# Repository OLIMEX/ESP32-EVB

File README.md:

# ESP32-EVB

ESP32 wifi / BLE development board with Ethernet, relays, microSD card, CAN, infrared, Li-Po charger, GPIOs.

Product page: https://www.olimex.com/Products/IoT/ESP32/ESP32-EVB/open-source-hardware

Open-source hardware board made with open-source CAD software. Comes with either ESP32-WROOM-32E or ESP32-WROOM-32UE module, depending on variant. Board vairants are:

| Board variant | ESP32 module  | External antenna  | Temperature range |
| ------------- | ------------- | -------------  | ------------- |
| ESP32-EVB     | ESP32-WROOM-32E  | No  | 0-70°C  |
| ESP32-EVB-EA  | ESP32-WROOM-32UE  | Yes  | 0-70°C  |
| ESP32-EVB-EA-IND  | ESP32-WROOM-32UE  | Yes  | -40+85°C |
| ESP32-EVB-IND  | ESP32-WROOM-32E  | No  | -40+85°C |

ESP32-EVB - ESP32-WROOM-32E module, no external antenna, commercial temeprature range 0-70°C

ESP32-EVB-EA - ESP32-WROOM-32UE module, fitting external antenna, commercial temeprature range 0-70°C

ESP32-EVB-EA-IND - ESP32-WROOM-32UE module, fitting external antenna, industrial temeprature range -40+85°C

ESP32-EVB-IND - ESP32-WROOM-32E module, no external antenna, industrial temeprature range -40+85°C

You can find design hardware sources, schematic exports, BOMs, and more, in the "HARDWARE" folder.

You can find ESP-IDF and Arduino IDE examples, in the "SOFTWARE" folder.

# FAQ

---

**Q:** I have some trouble downloading my code to ESP32-EVB. Is there a way to force boot mode?

**A:** By default the board comes without BOOT button functioanlity. However, we have providedan option to can convert user BUT1 into BOOT button to force button but this requires hardware change and soldering. Soldering experience is required since it is a tight spot. You need to perform two changes:

- Solder the pads of R46 together (or solder 0R resistor in 0603 size in the R46 position there);
- Unsolder R14 and solder its pads together (or again solder 0R resistor in 0603 size in the R14 position).

After the two changes, to manually force boot mode, hold button BUT1 then reset the board with RST1. Both R46 and R14 are near the button BUT1. Notice that the button will still act as user button after the initial boot sequence. You can find more about what changing these resistors does if you inspect the schematic.

---

**Q:** The Ethernet doesn't start after a restart, it throws "init phy failed" error. What should I do?

**A:** Ethernet might hang of initialized too quickly after a reset. Add some delay at the start of the code before the Ethernet initialization. For example, if you are using the default Arduino IDE demo for LAN8720 try adding delay () after Serial.begin(), as shown below:
```
void setup()
{
Serial.begin(115200);
delay (2000);
WiFi.onEvent(WiFiEvent);
ETH.begin();
}
```

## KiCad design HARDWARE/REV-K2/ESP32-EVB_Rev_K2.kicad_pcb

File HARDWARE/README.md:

# ESP32-EVB

Hardware revisions changes:

- revision A - internal, not released
- revision B - initial public release
- revision C - changes:

1. MicroUSB connector moved back, 40 mils to the middle of the board.
2. All mounting holes are now connected to GND.
3. Improved the ground layer around the infra red's pads and wires.

- revision C1 - changes:

1. Changed R38 from 10k/0603 to 100k/0603 to lower the time without clock
2. Changed C28 from 100n/0603 to 10n/0603 to increase the time in reset

- revision D - changes:

1. Added a resistor (1k) between OSC_DIS and reset of the PHY.
2. Added option to use MCP2562-E/SN and SN65HVD230D upotreba -> R58(NA/R0603)!
4. U2 be promeneno ot SY8009AAAC(SOT23-5) na SY8089AAAC(SOT23-5).
5. FET1 and FET2 were changed from IRLML6402 to WPM2015-3/TR.

- revision D1 - changes:

1. Removed C18(10uF)
2. U8 changed from BD5230G-TR(SSOP5/SOT-23-5) to NCP303LSN27T1G(SOT-23-5), due to unavailability;
3. C28 changed from 100nF/50V/20%/Y5V/C0603 to 470nF/16V/10%/X7R/C0603, because of the U8 change;

- revision D2 - changes:

1. U6 changed from MCP2551-I/SN(SOIC-8_150mil) to MCP2562-E/SN(SOIC-8_150mil)
2. R58 changed from NA/R0603 to 0R/R0603.

- revision E - changes:

MCP2551 got "Not recommended for new designs" status so it is replaced with MCP2562 and this lead to:

1. R58(0R/R0603) was deleted and U6's pin<5> was connected to +3.3V.
2. R52(680R/R0603) was deleted.
3. R50(330R/R0603) and R51(330R/R0603) were deleted.
4. The MCP2562-E_SN(SOIC-8_150mil)'s symbol was updated, i,.e. U6's component was exchanged with 2562!

Changes related to the problems with ethernet PHY:

5. The following components were added to enable powering on the PHY after the 50MHz oscillator has been started: L5(NA(FB0805/600R/2A)), FET3(WPM2015-3/TR), FET4(BSS138), C29(22uF/6.3V/20%/X5R/C0603), R50(1k/R0603) and R51(10k/R0603).

Changes related to optimizations:

6. R26(330R/R0603) and R27(330R/R0603) were changed to 220R/R0603 to reserve a feeder.
7. C1 was changed from 47uF/6.3V/20%/X5R/C0805 to NA(47uF/6.3V/20%/X5R/C0805).	
8. C3 was changed from 47uF/6.3V/20%/X5R/C0805 to NA(47uF/6.3V/20%/X5R/C0805).

- revision F - changes:

1. BUT1 and RST1 new packages.
2. Minor PCB routing optimizations.
3. All footprints were updated.

- revision G - internal, not released

1. Changed the Li-Po charger to BL4054B (was MCP73833 previously).

- revision H - limited release, changes:

1. CH340 now powered only from USB (not from battery). Added D7 and D8 on TX/RX, levels are adjusted via R35 and R40. Pin #20 now disconnected. SY8089AAAC(SOT23-5) devider now R20 49.9k and R19 220k. R24 now 470ê.
2. Added battery voltage sense option. This is controlled with jumper BAT/BUT1, C30, R9, and R10. It is not enabled by default to maintain compatiblity with previous revisions.
3. Added 3D models of the components.
4. L2 now 2.2uH/1.5A/DCR=72mR/20%/3.00x3.00x1.50mm/CD32(NR3015T2R2M). Some improvements on ESP-WROOM-32_MODULE package.

- revision H1 - released, changes:

Improved start up for certain hardware setups. Revision H1 has same PCB as revision H (and the PCB of revision H1 says "H") but couple of component changes:

1. Changed R24 from 470k/0603 to 1k/0603, the 1k resistor is soldered over the 470k one to reduce chances of damage.

- revsion I - released, changes:

Applied the changes from revision H1 to the PCB and the design, and further improved start-up reliability by adding a capacitor:

1. Added C31(1uF/10V/10%/X5R/C0603) on the ESP_EN signal and R24's value changed from 1k/0603 to 10k/0603;
2. Added several text lables at the botttom of the board about CAN's connector signals and the battery polarity.

- revision I1 - released, changes:

1. Changed C18 from NA(10uF/6.3V/20%/X5R/C0603) to 1nF/50V/5%/NPO(COG)/C0603 - this improves Ethernet reliability during relay switcing;

- revision I2 - released, changes:

1. Changed U8, from NCP303LSN27T1G(SOT-23-5) to NCP303LSN18T1G(SOT-23-5).

- revision I3 - released, changes:

1. Changed U6 from MCP2562-E/SN(SOIC-8_150mil) to SIT1042T/3(SOIC-8_150mil).

- revision I4 - released

1. Changed U2 value to NCV303LSN23T1G.

- revision J - not released

1. Due to global unavailability of MCP2562-E/SN chips, it was necessary to adjust the CAN schematic for compatiblity with MCP2551/SIT1050 too. Following changes were required:
- U6 changed from MCP2562-E/SN(SOIC-8_150mil) to SIT1050T(SOIC-8_150mil);
- Added R12, NA/R0603;
- Added R13, 330R/R0603;
- Added R15, 680R/R0603;
2. CE sign added in the PCB;
3. Changed C18 from NA(10uF/6.3V/20%/X5R/C0603) to 1nF/50V/5%/NPO(COG)/C0603 - this improves Ethernet behavior during relay switching;
4. Added U11(VDA2710NTA(SOT-23)), D10(BAT54A(SOT23-3)), R58(49.9R/1%/R0402), R52(220k/R0603) and C32(1uF/10V/10%/X5R/C0603), so that we can have option to replace the reset chip NCP303LSN27T1G(SOT-23-5). Changed U8 to (NA(NCP303LSN27T1G(SOT-23-5))) and C28 to NA(470nF/16V/10%/X7R/C0603);
5. Added D9(1N5819S4(SOD-123)), to rptoect ESP_EN from 4.2V surge during programming; also to protect C32 gettomg cjarged from DTR output of CH340, else new reset schematic (VDA2710NTA) has random timing after pressing reset button;
6. Added ESD protection on the Ethernet, TVS1(ESDS314DBVR(SOT-23-5));
7. R28, R31, R32, and R33 changed from 49.9R/1%/R0603 to 49.9R/1%/R0402;
8. U7 changed from RPM7236-H8 to VS1838B.

- revision K - released

1. Labelling improvements;
2. Removed "GPIO4" from the "Internal Bootstrapping Resistors" table.

- revision K1 - released

1. Changed reset IC from VDA2710NTA(SOT-23)to HX7027 (due to unavailability of VDA2710NTA).
2. HX7027 has slightly bigger consumption and when powered trought R52 the voltage might get too low; so also changed R52 from 220k to 100k.

- revision K2 - released
------
1. Changed battery chager to TP4054-42-SOT25-R;
2. Changed R8 from 2k to 10k to reduce battery charger current to 100mA.

- revision L - released
------

1. Migated the whole project to KiCad7;
2. R57 deleted to reduce possible environment noise picking in combination with relay switching;
3. Relays changed;
4. U2-SY8089 changed to TPS62A02ADRLR(SOT-563-6);
5. CH340 changed with smaller variant ch340X.

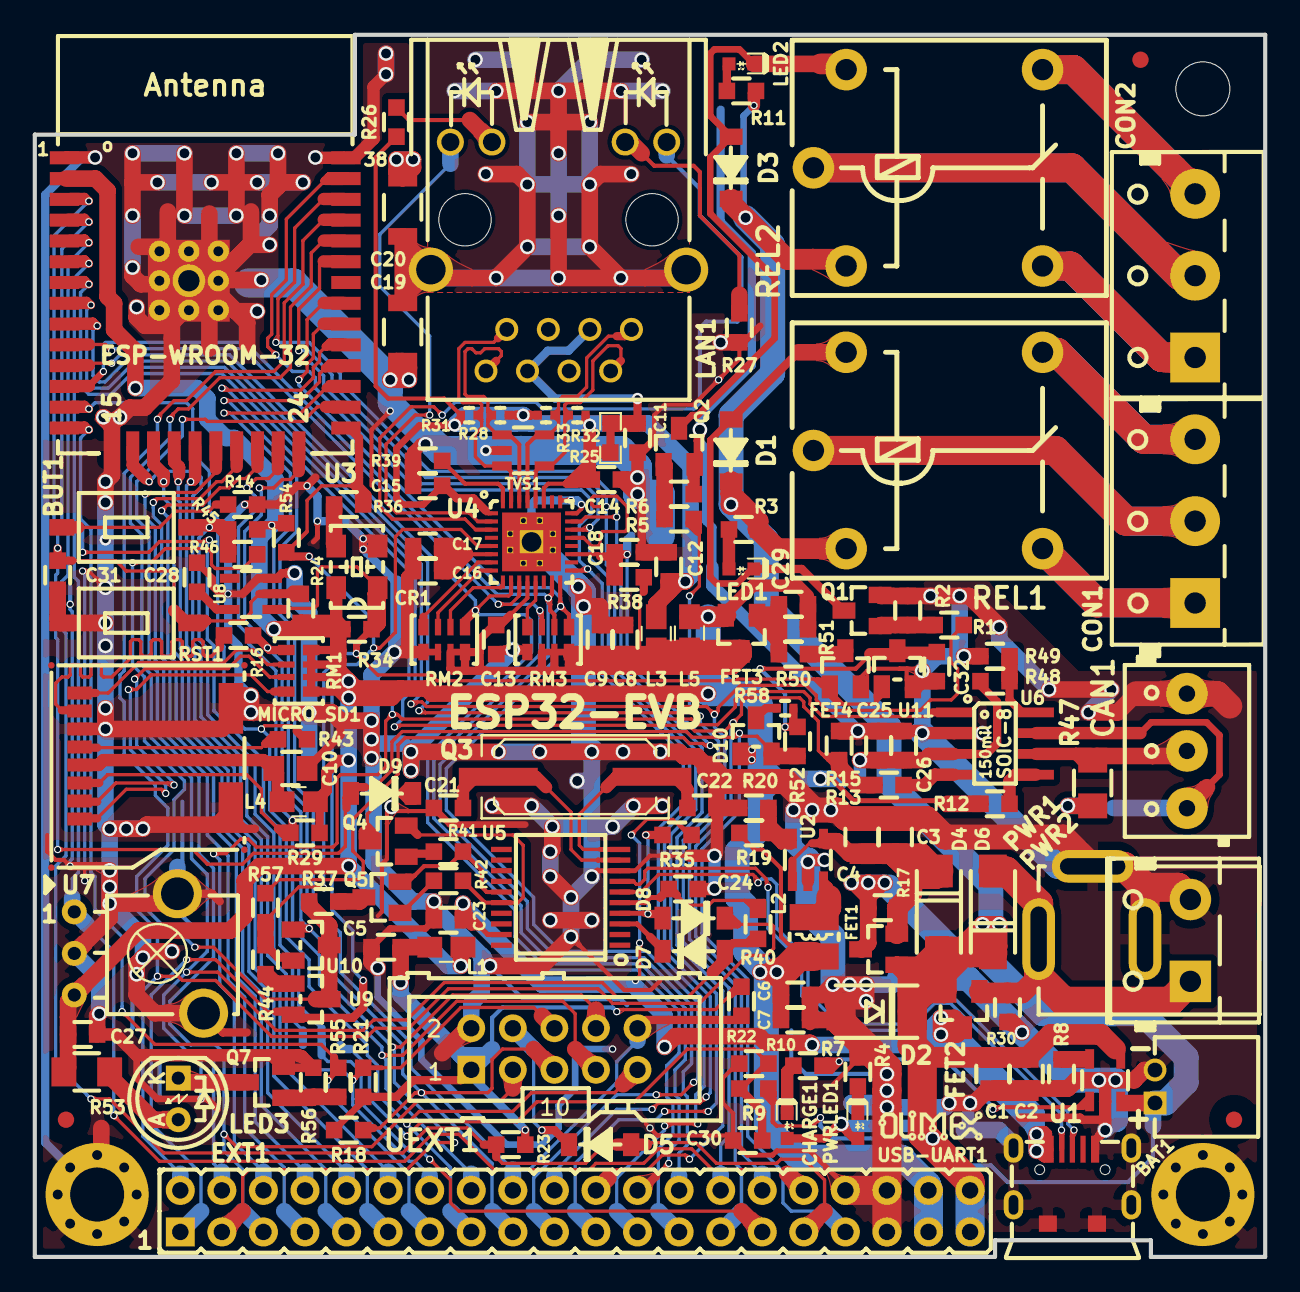
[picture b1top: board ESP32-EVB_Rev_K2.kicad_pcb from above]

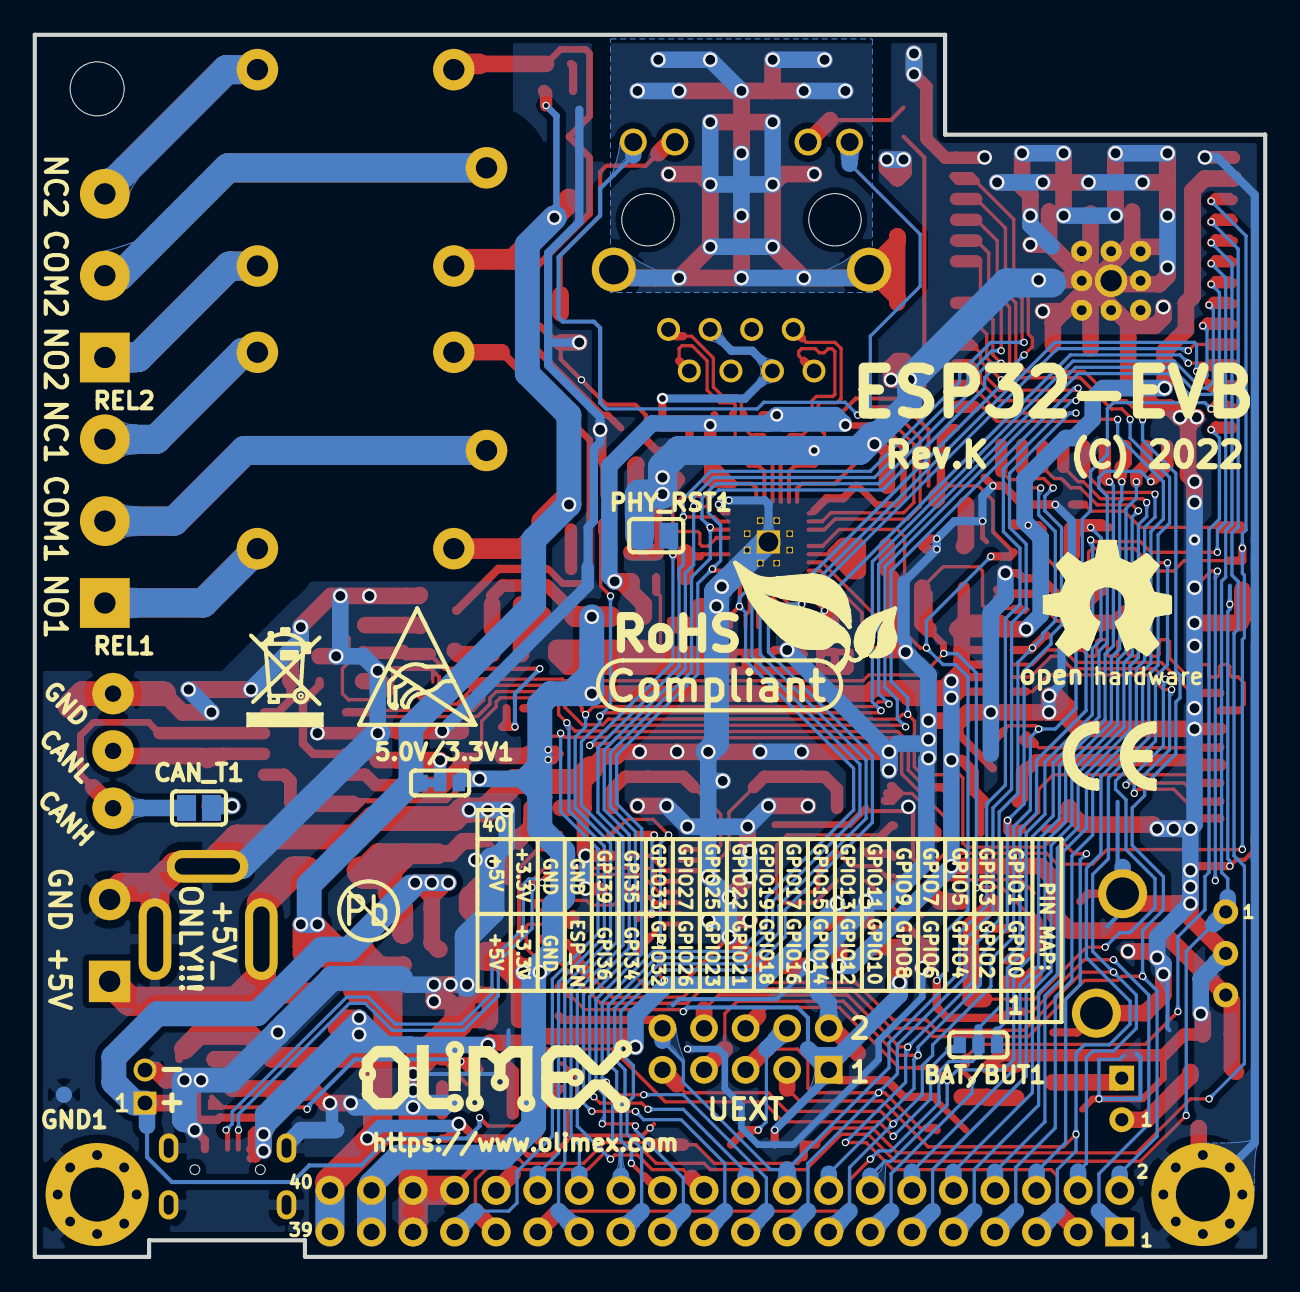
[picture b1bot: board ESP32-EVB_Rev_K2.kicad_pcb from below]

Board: 2 copper layers, 75.2 x 74.7 mm, 170 parts (12 on the bottom side), 120 nets.

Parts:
5.0V/3.3V1: Closed(1-2)/Opened(2-3); SJ_2_SMALL_12_TIED
BAT1: DW02R; LIPO_BAT-CON2DW02R
BAT/BUT1: Opened(2-3)/Soldered(1-2); SJ_2_SMALL
BUT1: T1107A(6x3,8x2,5MM)
C1, C3: NA(47uF/6.3V/20%/X5R/C0805); C_0805_5MIL_DWS
C2, C4, C10: 47uF/6.3V/20%/X5R/C0805; C_0805_5MIL_DWS
C5, C6, C7, C8, C9, C12, C23, C29: 22uF/6.3V/20%/X5R/C0603; C_0603_5MIL_DWS
C11, C13, C14, C15, C17, C24, C25, C27, C30: 100nF/50V/20%/Y5V/C0603; C_0603_5MIL_DWS
C16: 2.2uF/6.3V/10%/X5R/C0603; C_0603_5MIL_DWS
C18: 1nF/50V/5%/NPO(COG)/C0603; C_0603_5MIL_DWS
C19: 1nF/2000V/10%/X7R/C1206; C_1206_5MIL_DWS_ISO
C20: NA(1nF/2000V/10%/X7R/C1206); C_1206_5MIL_DWS_ISO
C21, C22: 27pF/50V/5%/C0G/C0603; C_0603_5MIL_DWS
C26: 10uF/6.3V/20%/X5R/C0603; C_0603_5MIL_DWS
C28: NA(470nF/16V/10%/X7R/C0603); C_0603_5MIL_DWS
C31, C32: 1uF/10V/10%/X5R/C0603; C_0603_5MIL_DWS
CAN1: TB3-3.5ММ(HD-351 3P); TB3-3.5mm
CAN_T1: Opened; SJ
CHARGE1: LED/Yellow/0603; LED_0603_KA
CON1, CON2: DG306-5.0-3P; TB3-DG306-5.0_3P
CR1: Q50MHz/25ppm/3V/4P/5x3.2mm; 5032-4P_HCX-3S
D1, D3, D5, D7, D8, D9: 1N5819S4(SOD-123); SOD-123_1C-2A_KA
D2: SMBJ6.0A(DO-214AA); DO214AA_1(K)-2(A)
D4, D6: 1N5822/SS34/SMA; SMA-KA
D10: BAT54A(SOT23-3); SOT23-3
EXT1: NA(HN2x20); HN2x20
FET1, FET2, FET3: WPM2015-3/TR; SOT23
FET4: BSS138; SOT23
Fid1, Fid2, Fid3: Fiducial1x3
GND1: TESTPAD; TESTPAD_40-ROUND
L1, L3, L4: 600R/2A/UPZ2012E-601-2R0TF; L_0805_5MIL_DWS
L2: 2.2uH/NRS3015T2R2MNGH; CD32
L5: NA(FB0805/600R/2A); L_0805_5MIL_DWS
LAN1: RJLBC-060TC1(LPJ4013EDNL); RJLBC-060TC1
LED1, LED2: LED/GREEN/0603; LED_0603_KA
LED3: LED/IR333-A/5mm; LED-5mm-PTH-AK
Logo-OSHW: LOGO_OPENHARDWARE_8x8
Logo-Olimex-Big: OLIMEX_LOGO_TB
Logo-Olimex_Small: LOGO_OLIMEX_80
MH1: Mounting_hole_Shield_3.3mm; Mounting_hole_3.3mm
MH2, MH3: Mounting_hole_Shield_3.3mm
MICRO_SD1: TFC-WXCP11-08-LF
PHY_RST1: Opened; SJ
PWR1: PWRJ-2mm(YDJ-1134); PWRJ-2mm(YDJ-1136)
PWR2: NA(TB2 DG306-5.0-2P); TB2-DG306-5.0_2P
PWRLED1: LED/RED/0603; LED_0603_KA
Q1, Q2, Q4, Q5, Q7: BC817-40(SOT23); SOT23
Q3: Q12MHz/2P/20ppm/20pF/HU49SM; Q_49U3HMS
R1, R5, R41, R42, R50, R55: 1k/R0603; R_0603_5MIL_DWS
R2, R6, R22, R23, R24, R29, R30, R34, R35, R38, R40, R45, R49, R51, R56: 10k/R0603; R_0603_5MIL_DWS
R3, R4, R7, R11, R18, R21: 2.2k/R0603; R_0603_5MIL_DWS
R8: 2k/1%/R0603; R_0603_5MIL_DWS
R9, R10: 470k/R0603; R_0603_5MIL_DWS
R12, R17, R44, R46, R48, R54: NA/R0603; R_0603_5MIL_DWS
R13: 330R/R0603; R_0603_5MIL_DWS
R14, R16, R26, R27, R37: 220R/R0603; R_0603_5MIL_DWS
R15: 680R/R0603; R_0603_5MIL_DWS
R19: 220k/R0603; R_0603_5MIL_DWS
R20: 49.9k/1%/R0603; R_0603_5MIL_DWS
R25: 0R(board_mounted); 0R_0603
R28, R31, R32, R33, R58: 49.9R/1%/R0402; R_0402_5MIL_DWS
R36, R43: 10R/R0603; R_0603_5MIL_DWS
R39: 12.1k/1%/R0603; R_0603_5MIL_DWS
R47: 120R/R1206; R_1206_5MIL_DWS
R52: 100k/R0603; R_0603_5MIL_DWS
R53: 6.8R/R1206; R_1206_5MIL_DWS
R57: NA(1k/R0603); R_0603_5MIL_DWS
REL1, REL2: RAS-0515 (LEG-5); Relay_RAS-05-15
RM1, RM2, RM3: RA1206_(4X0603)_4B8_2.2k; R_MATRIX_4
RST1: T1107A(6x3,8x2,5MM)
Sign-Antistatic: Val**; LOGO_ANTISTATIC_1
Sign-PbFree: LOGO_PBFREE
Sign-RecycleBin: LOGO_RECYCLEBIN_1
Sign-RoHS: Val**; LOGO_ROHS_1
Sign_CE: CE_Sign
TVS1: ESDS314DBVR(SOT-23-5); SOT-23-5
U1: TP4054-42-SOT25-R; SOT-23-5
U2: SY8089AAAC(SOT23-5); SOT-23-5
U3: ESP32-WROOM-32E-N4; ESP-WROOM-32_MODULE
U4: LAN8710A-EZC(QFN32); QFN32_EP(33)_5.00x5.00x0.90mm_Pitch_0.50mm
U5: CH340T(SSOP20W); SSOP-20W
U6: SIT1050T(SOIC-8_150mil); SOIC-8_150mil
U7: VS1838B; RPM7236-H8
U8: NA(NCP303LSN27T1G(SOT-23-5)); SOT-23-5
U9, U10: BAT54C(SOT23-3); SOT23-3
U11: HX7027(SOT-23); SOT-23
UEXT1: BH10S(B-D-02x5-LF); UEXT_ML10
USB-UART1: MISB-SWMM-5B-LF; USB-MICRO_MISB-SWMM-5B_LF

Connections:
+3.3V: 5.0V/3.3V1.3, C6.1, C7.1, C27.1, C29.1, CR1.4, D10.1, EXT1.37, EXT1.38, FET3.2, L1.1, L2.2, L4.1, L5.1, R12.1, R19.2, R24.1, R29.1, R34.1, R45.1, R51.1, R53.1, R54.2, RM1.1.2, RM1.2.2, RM1.3.2, RM1.4.2, U3.2, U7.3
+3.3VLAN: C8.1, C9.1, C13.1, FET3.3, L3.1, L5.2, R38.2, RM2.3.1, RM2.4.1, RM3.1.2, RM3.2.2, RM3.3.2, U4.12
+5V: 5.0V/3.3V1.1, C1.1, C2.1, CHARGE1.2, D1.1, D2.1, D3.1, D4.2, D6.1, EXT1.39, EXT1.40, FET1.1, FET2.2, PWRLED1.2, R3.1, R11.1, REL1.1, REL2.1, U1.4
/+5V_EXT: D6.2, FET2.1, PWR1.+, PWR2.1, R30.1
/+5V_USB: C23.1, FET2.3, R35.1, U5.19, USB-UART1.1
/BUT1: BAT/BUT1.1, BUT1.1, R45.2, R46.1
/CANH: CAN1.3, CAN_T1.2, U6.7
/CANL: CAN1.2, R47.2, U6.6
/D_Com: R37.2, R46.2, U9.3, U10.3
/ESP_EN: C31.2, D9.2, D10.2, EXT1.33, R24.2, R52.2, RST1.1, U3.3, U8.2
/GPI34/BUT1: BAT/BUT1.2, EXT1.29, U3.6
/GPI35/CAN-RX: EXT1.30, R13.1, R15.1, U3.7
/GPI36/U1RXD: D5.2, EXT1.31, R23.2, U3.4
/GPI39/IR_RECEIVE: EXT1.32, U3.5, U7.1
/GPIO0/XTAL1/CLKIN: EXT1.1, R36.2, R54.1, U3.25, U4.5, U9.2
/GPIO1/U0TXD: D8.1, EXT1.2, U3.35
/GPIO2/HS2_DATA0: EXT1.3, R16.1, RM1.1.1, U3.24, U10.1, UEXT1.8
/GPIO3/U0RXD: D7.2, EXT1.4, R40.2, U3.34
/GPIO4/U1TXD: EXT1.5, U3.26, UEXT1.3
/GPIO5/CAN-TX: EXT1.6, U3.29, U6.1
/GPIO6/SD_CLK: EXT1.7, U3.20
/GPIO7/SD_DATA0: EXT1.8, U3.21
/GPIO8/SD_DATA1: EXT1.9, U3.22
/GPIO9/SD_DATA2: EXT1.10, U3.17
/GPIO10/SD_DATA3: EXT1.11, U3.18
/GPIO11/SD_CMD: EXT1.12, U3.19
/GPIO12/IR_Transmit: EXT1.13, R55.1, U3.14
/GPIO13/I2C-SDA: EXT1.14, R21.2, U3.16, UEXT1.6
/GPIO14/HS2_CLK: EXT1.15, R43.1, U3.13, UEXT1.9
/GPIO15/HS2_CMD: EXT1.16, MICRO_SD1.3, R29.2, U3.23, UEXT1.7
/GPIO16/I2C-SCL: EXT1.17, R18.2, U3.27, UEXT1.5
/GPIO17/SPI_CS: EXT1.18, R22.2, U3.28, UEXT1.10
/GPIO18/MDIO(RMII): EXT1.19, RM3.1.1, U3.30, U4.16
/GPIO19/EMAC_TXD0(RMII): EXT1.20, U3.31, U4.22
/GPIO21/EMAC_TX_EN(RMII): EXT1.21, U3.33, U4.21
/GPIO22/EMAC_TXD1(RMII): EXT1.22, U3.36, U4.23
/GPIO23/MDC(RMII): EXT1.23, U3.37, U4.17
/GPIO25/EMAC_RXD0(RMII): EXT1.24, RM3.3.1, U3.10, U4.11
/GPIO26/EMAC_RXD1(RMII): EXT1.25, RM2.4.2, U3.11, U4.10
/GPIO27/EMAC_RX_CRS_DV: EXT1.26, RM3.2.1, U3.12, U4.15
/GPIO32/REL1: EXT1.27, R1.1, U3.8
/GPIO33/REL2: EXT1.28, R5.1, U3.9
/OSC_DIS: CR1.1, FET4.1, R34.2, R44.1, R57.2, U8.1, U10.2, U11.1
/PHYAD0: RM3.4.1, U4.13
/PHYAD1: RM2.1.2, U4.7
/PHYAD2: RM2.2.2, U4.8
/RMIISEL: RM2.3.2, U4.9
/RXN-: LAN1.8, R28.2, TVS1.1, U4.30
/RXP+: LAN1.7, R31.2, TVS1.3, U4.31
/TXN-: LAN1.2, R32.2, TVS1.4, U4.28
/TXP+: LAN1.1, R33.2, TVS1.5, U4.29
/VDD1A-2A: C12.1, C14.1, C15.1, L3.2, R25.1, R26.1, R28.1, R31.1, R32.1, R33.1, U4.1, U4.27
/VDDCR: C16.1, C17.1, U4.6
GND: BAT1.2, C1.2, C2.2, C3.2, C4.2, C5.1, C6.2, C7.2, C8.2, C9.2, C10.2, C11.2, C12.2, C13.2, C14.2, C15.2, C16.2, C17.2, C18.1, C19.2, C20.2, C21.2, C22.2, C23.2, C24.2, C25.1, C26.1, C27.2, C28.2, C30.2, C31.1, C32.1, CAN1.1, CR1.2, D2.2, EXT1.34, EXT1.35, EXT1.36, FET4.2, GND1.1, MH2.GND1, MH3.GND1, MICRO_SD1.6, MICRO_SD1.SH1, MICRO_SD1.SH2, PHY_RST1.1, PWR1.-, PWR2.2, Q1.2, Q2.2, Q7.2, R2.1, R4.2, R6.1, R8.1, R10.2, R14.2, R15.2, R20.2, R27.2, R30.2, R39.2, R49.2, R56.1, RM2.1.1, RM2.2.1, RM3.4.2, RST1.2, TVS1.2, U1.2, U2.2, U3.1, U3.15, U3.38, U3.39, U4.24, U4.25, U4.33, U5.8, U6.2, U7.0, U7.2, U8.3, U11.2, UEXT1.2, USB-UART1.0, USB-UART1.5
unnamed: 5.0V/3.3V1.2, C25.2, C26.2, R48.2, U6.3
unnamed: BAT1.1, FET1.3, R9.1, R17.1, U1.3
unnamed: BAT/BUT1.3, C30.1, R9.2, R10.1
unnamed: BUT1.2, R14.1
unnamed: C3.1, C4.1, D4.1, FET1.2, R17.2, U2.1, U2.4
unnamed: C5.2, L1.2, R18.1, R21.1, R22.1, R23.1, UEXT1.1
unnamed: C10.1, L4.2, MICRO_SD1.4
unnamed: C11.1, LAN1.3, LAN1.6, R25.2
unnamed: C18.2, PHY_RST1.2, R38.1, R57.1, U4.19
unnamed: C19.1, C20.1, LAN1.GND1, LAN1.GND2
unnamed: C21.1, Q3.1, U5.9
unnamed: C22.1, Q3.2, U5.10
unnamed: C24.1, R40.1, U5.5
unnamed: C28.1, U8.5
unnamed: C29.2, FET3.1, R50.2, R51.2
unnamed: C32.2, R52.1, R58.2, U11.3
unnamed: CAN_T1.1, R47.1
unnamed: CHARGE1.1, R7.2
unnamed: CON1.1, REL1.NO0
unnamed: CON1.2, REL1.COM0
unnamed: CON1.3, REL1.NC0
unnamed: CON2.1, REL2.NO0
unnamed: CON2.2, REL2.COM0
unnamed: CON2.3, REL2.NC0
unnamed: CR1.3, R36.1
unnamed: D1.2, LED1.1, Q1.3, REL1.2
unnamed: D3.2, LED2.1, Q2.3, REL2.2
unnamed: D5.1, UEXT1.4
unnamed: D7.1, U5.3
unnamed: D8.2, R35.2, U5.4
unnamed: D9.1, Q4.3
unnamed: D10.3, R58.1
unnamed: FET4.3, R50.1
unnamed: L2.1, U2.3
unnamed: LAN1.AG1, R26.2
unnamed: LAN1.AY1, U4.3
unnamed: LAN1.KG1, U4.2
unnamed: LAN1.KY1, R27.1
unnamed: LED1.2, R3.2
unnamed: LED2.2, R11.2
unnamed: LED3.1, R53.2
unnamed: LED3.2, Q7.3
unnamed: MICRO_SD1.1, RM1.4.1
unnamed: MICRO_SD1.2, RM1.3.1
unnamed: MICRO_SD1.5, R43.2
unnamed: MICRO_SD1.7, R16.2
unnamed: MICRO_SD1.8, RM1.2.1
unnamed: PWRLED1.1, R4.1
unnamed: Q1.1, R1.2, R2.2
unnamed: Q2.1, R5.2, R6.2
unnamed: Q4.1, R41.2
unnamed: Q4.2, R42.1, U5.16
unnamed: Q5.1, R42.2
unnamed: Q5.2, R41.1, U5.15
unnamed: Q5.3, R37.1
unnamed: Q7.1, R55.2, R56.2
unnamed: R7.1, U1.1
unnamed: R8.2, U1.5
unnamed: R12.2, U6.5
unnamed: R13.2, U6.4
unnamed: R19.1, R20.1, U2.5
unnamed: R39.1, U4.32
unnamed: R44.2, U9.1
unnamed: R48.1, R49.1, U6.8
unnamed: U5.6, USB-UART1.3
unnamed: U5.7, USB-UART1.2

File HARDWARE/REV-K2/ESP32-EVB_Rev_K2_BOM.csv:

"Id";"Designator";"Package";"Quantity";"Designation";"Supplier and ref";
1;"PWR2";"TB2-DG306-5.0_2P";1;"NA(TB2 DG306-5.0-2P)";;;
2;"PWR1";"PWRJ-2mm(YDJ-1136)";1;"PWRJ-2mm(YDJ-1134)";;;
3;"UEXT1";"UEXT_ML10";1;"BH10S(B-D-02x5-LF)";;;
4;"U3";"ESP-WROOM-32_MODULE";1;"ESP32-WROOM-32E-N4";;;
5;"R33,R32,R28,R31,R58";"R_0402_5MIL_DWS";5;"49.9R/1%/R0402";;;
6;"R43,R36";"R_0603_5MIL_DWS";2;"10R/R0603";;;
7;"EXT1";"HN2x20";1;"NA(HN2x20)";;;
8;"CAN1";"TB3-3.5mm";1;"TB3-3.5ММ(HD-351 3P)";;;
9;"LAN1";"RJLBC-060TC1";1;"RJLBC-060TC1(LPJ4013EDNL)";;;
10;"REL2,REL1";"Relay_RAS-05-15";2;"RAS-0515 (LEG-5)";;;
11;"BAT1";"LIPO_BAT-CON2DW02R";1;"DW02R";;;
12;"D4,D6";"SMA-KA";2;"1N5822/SS34/SMA";;;
13;"D5,D7,D8,D3,D1,D9";"SOD-123_1C-2A_KA";6;"1N5819S4(SOD-123)";;;
14;"Q3";"Q_49U3HMS";1;"Q12MHz/2P/20ppm/20pF/HU49SM";;;
15;"USB-UART1";"USB-MICRO_MISB-SWMM-5B_LF";1;"MISB-SWMM-5B-LF";;;
16;"BUT1,RST1";"T1107A(6x3,8x2,5MM)";2;"T1107A(6x3,8x2,5MM)";;;
17;"U6";"SOIC-8_150mil";1;"SIT1050T(SOIC-8_150mil)";;;
18;"U5";"SSOP-20W";1;"CH340T(SSOP20W)";;;
19;"MICRO_SD1";"TFC-WXCP11-08-LF";1;"TFC-WXCP11-08-LF";;;
20;"U4";"QFN32_EP(33)_5.00x5.00x0.90mm_Pitch_0.50mm";1;"LAN8710A-EZC(QFN32)";;;
21;"Sign_CE";"CE_Sign";1;"CE_Sign";;;
22;"CON2,CON1";"TB3-DG306-5.0_3P";2;"DG306-5.0-3P";;;
23;"LED3";"LED-5mm-PTH-AK";1;"LED/IR333-A/5mm";;;
24;"U7";"RPM7236-H8";1;"VS1838B";;;
25;"CR1";"5032-4P_HCX-3S";1;"Q50MHz/25ppm/3V/4P/5x3.2mm";;;
26;"R29,R56,R49,R45,R30,R40,R38,R35,R34,R24,R23,R22,R6,R2,R51";"R_0603_5MIL_DWS";15;"10k/R0603";;;
27;"C2,C4,C10";"C_0805_5MIL_DWS";3;"47uF/6.3V/20%/X5R/C0805";;;
28;"Fid2,Fid1,Fid3";"Fiducial1x3";3;"";;;
29;"R25";"0R_0603";1;"0R(board_mounted)";;;
30;"D2";"DO214AA_1(K)-2(A)";1;"SMBJ6.0A(DO-214AA)";;;
31;"R57";"R_0603_5MIL_DWS";1;"NA(1k/R0603)";;;
32;"R44,R54,R48,R46,R17,R12";"R_0603_5MIL_DWS";6;"NA/R0603";;;
33;"U10,U9";"SOT23-3";2;"BAT54C(SOT23-3)";;;
34;"Sign-RoHS";"LOGO_ROHS_1";1;"Val**";;;
35;"Sign-RecycleBin";"LOGO_RECYCLEBIN_1";1;"";;;
36;"Sign-PbFree";"LOGO_PBFREE";1;"";;;
37;"Logo-OSHW";"LOGO_OPENHARDWARE_8x8";1;"";;;
38;"Sign-Antistatic";"LOGO_ANTISTATIC_1";1;"Val**";;;
39;"R37,R27,R26,R16,R14";"R_0603_5MIL_DWS";5;"220R/R0603";;;
40;"C3,C1";"C_0805_5MIL_DWS";2;"NA(47uF/6.3V/20%/X5R/C0805)";;;
41;"R20";"R_0603_5MIL_DWS";1;"49.9k/1%/R0603";;;
42;"R19";"R_0603_5MIL_DWS";1;"220k/R0603";;;
43;"R4,R21,R18,R11,R3,R7";"R_0603_5MIL_DWS";6;"2.2k/R0603";;;
44;"R55,R42,R41,R5,R1,R50";"R_0603_5MIL_DWS";6;"1k/R0603";;;
45;"R53";"R_1206_5MIL_DWS";1;"6.8R/R1206";;;
46;"R47";"R_1206_5MIL_DWS";1;"120R/R1206";;;
47;"CAN_T1,PHY_RST1";"SJ";2;"Opened";;;
48;"C28";"C_0603_5MIL_DWS";1;"NA(470nF/16V/10%/X7R/C0603)";;;
49;"C27,C25,C24,C17,C15,C14,C13,C11,C30";"C_0603_5MIL_DWS";9;"100nF/50V/20%/Y5V/C0603";;;
50;"C26";"C_0603_5MIL_DWS";1;"10uF/6.3V/20%/X5R/C0603";;;
51;"C23,C12,C9,C8,C7,C6,C5,C29";"C_0603_5MIL_DWS";8;"22uF/6.3V/20%/X5R/C0603";;;
52;"C22,C21";"C_0603_5MIL_DWS";2;"27pF/50V/5%/C0G/C0603";;;
53;"C20";"C_1206_5MIL_DWS_ISO";1;"NA(1nF/2000V/10%/X7R/C1206)";;;
54;"C19";"C_1206_5MIL_DWS_ISO";1;"1nF/2000V/10%/X7R/C1206";;;
55;"MH3,MH2";"Mounting_hole_Shield_3.3mm";2;"Mounting_hole_Shield_3.3mm";;;
56;"R39";"R_0603_5MIL_DWS";1;"12.1k/1%/R0603";;;
57;"PWRLED1";"LED_0603_KA";1;"LED/RED/0603";;;
58;"LED2,LED1";"LED_0603_KA";2;"LED/GREEN/0603";;;
59;"GND1";"TESTPAD_40-ROUND";1;"TESTPAD";;;
60;"C18";"C_0603_5MIL_DWS";1;"1nF/50V/5%/NPO(COG)/C0603";;;
61;"C16";"C_0603_5MIL_DWS";1;"2.2uF/6.3V/10%/X5R/C0603";;;
62;"MH1";"Mounting_hole_3.3mm";1;"Mounting_hole_Shield_3.3mm";;;
63;"Logo-Olimex-Big";"OLIMEX_LOGO_TB";1;"";;;
64;"RM1,RM2,RM3";"R_MATRIX_4";3;"RA1206_(4X0603)_4B8_2.2k";;;
65;"U2";"SOT-23-5";1;"SY8089AAAC(SOT23-5)";;;
66;"Q1,Q4,Q5,Q7,Q2";"SOT23";5;"BC817-40(SOT23)";;;
67;"FET2,FET1,FET3";"SOT23";3;"WPM2015-3/TR";;;
68;"U8";"SOT-23-5";1;"NA(NCP303LSN27T1G(SOT-23-5))";;;
69;"L4,L3,L1";"L_0805_5MIL_DWS";3;"600R/2A/UPZ2012E-601-2R0TF";;;
70;"L2";"CD32";1;"2.2uH/NRS3015T2R2MNGH";;;
71;"5.0V/3.3V1";"SJ_2_SMALL_12_TIED";1;"Closed(1-2)/Opened(2-3)";;;
72;"FET4";"SOT23";1;"BSS138";;;
73;"L5";"L_0805_5MIL_DWS";1;"NA(FB0805/600R/2A)";;;
74;"Logo-Olimex_Small";"LOGO_OLIMEX_80";1;"";;;
75;"CHARGE1";"LED_0603_KA";1;"LED/Yellow/0603";;;
76;"U1";"SOT-23-5";1;"TP4054-42-SOT25-R";;;
77;"R8";"R_0603_5MIL_DWS";1;"2k/1%/R0603";;;
78;"BAT/BUT1";"SJ_2_SMALL";1;"Opened(2-3)/Soldered(1-2)";;;
79;"R9,R10";"R_0603_5MIL_DWS";2;"470k/R0603";;;
80;"C31,C32";"C_0603_5MIL_DWS";2;"1uF/10V/10%/X5R/C0603";;;
81;"R13";"R_0603_5MIL_DWS";1;"330R/R0603";;;
82;"R15";"R_0603_5MIL_DWS";1;"680R/R0603";;;
83;"TVS1";"SOT-23-5";1;"ESDS314DBVR(SOT-23-5)";;;
84;"D10";"SOT23-3";1;"BAT54A(SOT23-3)";;;
85;"R52";"R_0603_5MIL_DWS";1;"100k/R0603";;;
86;"U11";"SOT-23";1;"HX7027(SOT-23)";;;

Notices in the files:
HARDWARE/REV-A/ESP32-EVB_Rev_A.kicad_pcb:
(C) 2016
HARDWARE/REV-K2/ESP32-EVB_Rev_K2.kicad_pcb:
(C) 2022
